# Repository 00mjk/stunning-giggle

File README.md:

## Zasilacz Laboratoryjny 

Przedstawiam projekt zasilacza symetrycznego, +15/-15 Volt, opartego na popularnych linowowych scalonych stabilizatorach napięcia. Projekt przygotowany w KiCad, płytka drukowana jednostronna, do wykonania w domu, własnej pracowni, czy laboratorium. Poniżej schemat:

[schematics-diagram.pdf]( https://github.com/majsterklepka/stunning-giggle/raw/main/power-supply.pdf "Schemat ideowy")

W katalogu Gerber/ zamieszczone zostały pliki z rysunkiem płytki drukowanej, oczywiście w formacie Gerber.

## Credits

Całość projektu jest opublikowana na podstawie treści licencji: [CC-BY-SA 4.0](https://creativecommons.org/licenses/by-sa/4.0/ "license content") 

Projekt można wykorzystywać zarówno do swoich osobistych celów jak i do celów zarobkowych. Podobne projekty dostępne są w wielu firmach wytwarzających kity DIY, projekt powstał na własne zapotrzebowanie Autora i jest jego wyłączną własnością.

_MSc. Paweł Sobótka (SQ7EQE)_

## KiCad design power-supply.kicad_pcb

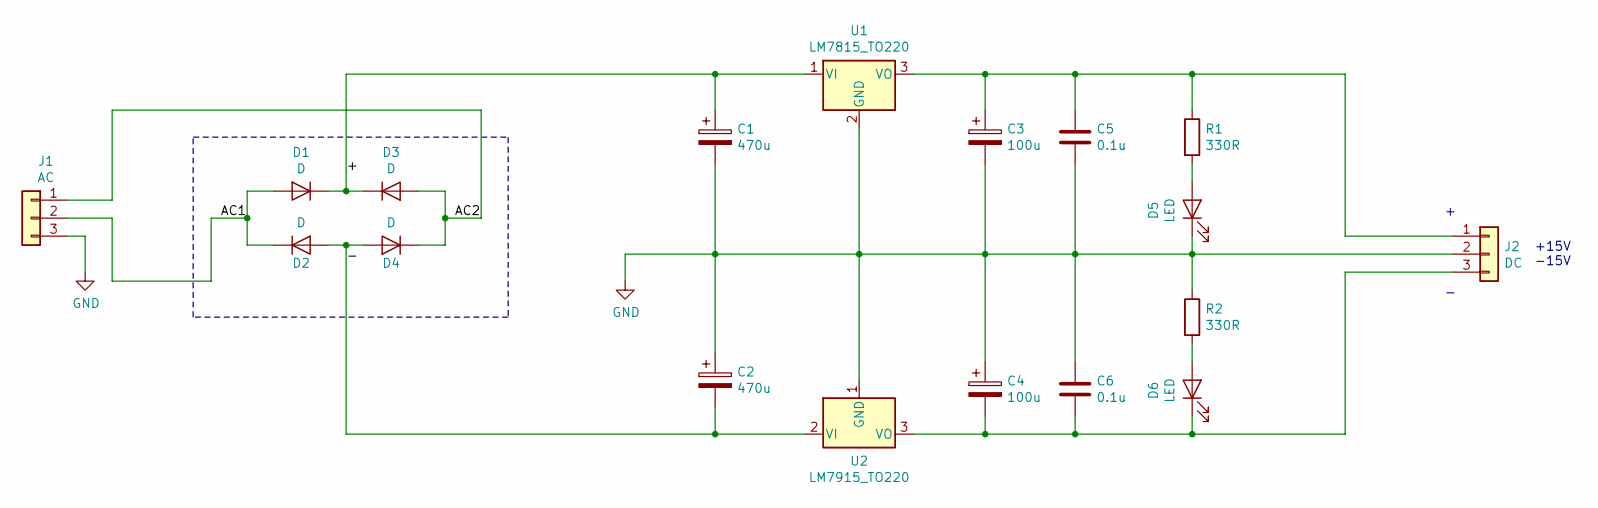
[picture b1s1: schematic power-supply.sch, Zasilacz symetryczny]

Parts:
C1, C2: 470u; CP_Radial_D8.0mm_P5.00mm
C3, C4: 100u; CP_Radial_D6.3mm_P2.50mm
C5, C6: 0.1u; C_Rect_L4.6mm_W3.0mm_P2.50mm_MKS02_FKP02
D1, D2, D3, D4: D; D_5W_P12.70mm_Horizontal
D5, D6: LED; LED_D3.0mm
J1: AC; TerminalBlock_Altech_AK300-3_P5.00mm
J2: DC; TerminalBlock_Altech_AK300-3_P5.00mm
R1, R2: 330R; R_Axial_DIN0207_L6.3mm_D2.5mm_P5.08mm_Vertical
U1: LM7815_TO220; TO-220-3_Horizontal_TabDown
U2: LM7915_TO220; TO-220-3_Horizontal_TabDown

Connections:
/+: C1.1, D1.1 (K), D3.1 (K), U1.1 (VI)
/-: C2.2, D2.2 (A), D4.2 (A), U2.2 (VI)
/AC1: D1.2 (A), D2.1 (K), J1.2
/AC2: D3.2 (A), D4.1 (K), J1.1
GND: C1.2, C2.1, C3.2, C4.1, C5.2, C6.1, D5.1 (K), J1.3, J2.2, R2.1, U1.2 (GND), U2.1 (GND)
unnamed: C3.1, C5.1, J2.1, R1.1, U1.3 (VO)
unnamed: C4.2, C6.2, D6.1 (K), J2.3, U2.3 (VO)
unnamed: D5.2 (A), R1.2
unnamed: D6.2 (A), R2.2

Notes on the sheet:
+15V -15V

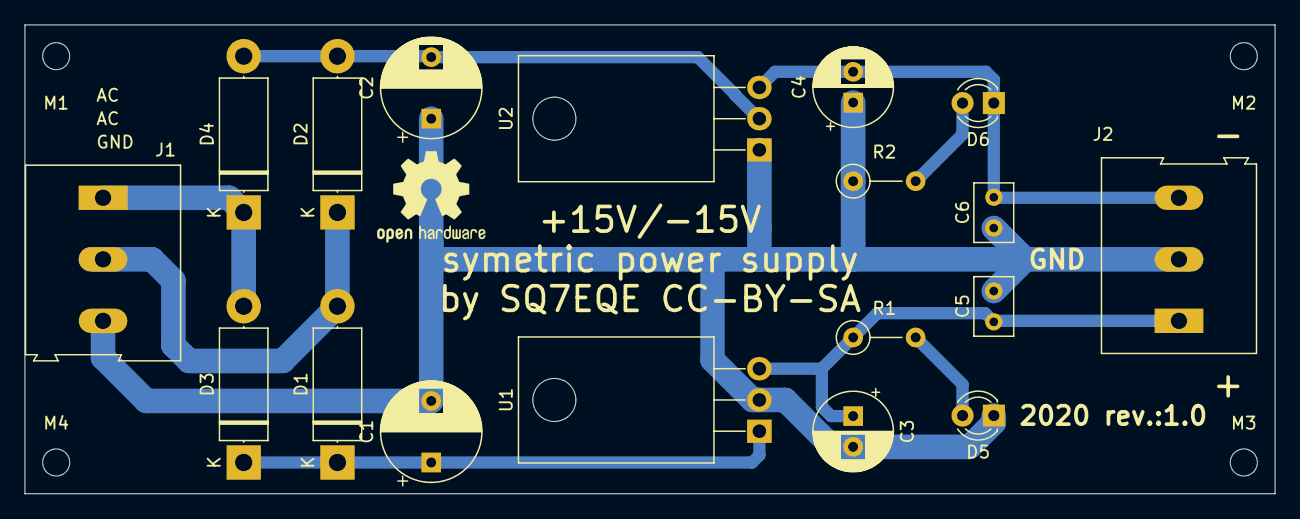
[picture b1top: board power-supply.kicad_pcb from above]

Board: 2 copper layers, 101.6 x 38.1 mm, 22 parts (0 on the bottom side), 9 nets.

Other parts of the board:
M1, M2, M3, M4: MountingHole_2.2mm_M2

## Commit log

2020-03-17 Set theme jekyll-theme-minimal
2020-03-17 update: update README.md
2020-03-17 update: new file
2020-03-17 update: update file
2020-03-18 update: update file with fresh layout
2020-04-03 new file
2020-04-03 update file
2020-04-07 update file, change size & redesign
2020-08-17 update
    add layouts with cookie policy scripts
2020-11-02 update
    I changed the value of the resistors to a more satisfactory one
2021-08-20 update broken links
2021-08-20 update broken grammarly
2021-08-20 update & recreate Gerber file
2021-08-20 update link name

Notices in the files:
power-supply.kicad_pcb:
by SQ7EQE CC-BY-SA
